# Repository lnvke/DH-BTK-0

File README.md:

# DH-BTK-0
Bluetooth keyboard HID device.

Made this so I can have a wireless keyboard while practicing with ESP-IDF BLE. Split would have given me the opportunity to work with peripheral bluetooth and non-HID communications, something I have never done before.

This is a custom integrated ESP32-C6 SoM based split keyboard using RMK rust mechanical keyboard firmware. Because Zephyr RTOS support for the ESP32-C6 is limited, ZMK firmware is not a viable choice for this project, as the HID (human interface) over GATT protocol has been documented to have conflicts between NimBLE and proprietary Espressif BLE controllers. RMK uses TrouBLE, a rust-based BLE host stack for bluetooth general functionality, which allows for direct interface with esp-radio, taking the role of the connecting link between TrouBLE and the internal host controller interface for bluetooth.
CAD:
https://cad.onshape.com/documents/ec01e30260fb570aa777a2a3 

PCB/Schematic:

(higher quality in SVG)

To make this for yourself, simply download the gerber files found in the production folder (seen as zip files) and export to your fab of choice. I used JLCPCB here. This PCB was designed to be completely double-sided and interchangeable, as to cut down on PCB manufacturing costs. Using JLCPCB's PCB fab MOQ of 5, you can make up to 2 of these keyboards given you have enough components.

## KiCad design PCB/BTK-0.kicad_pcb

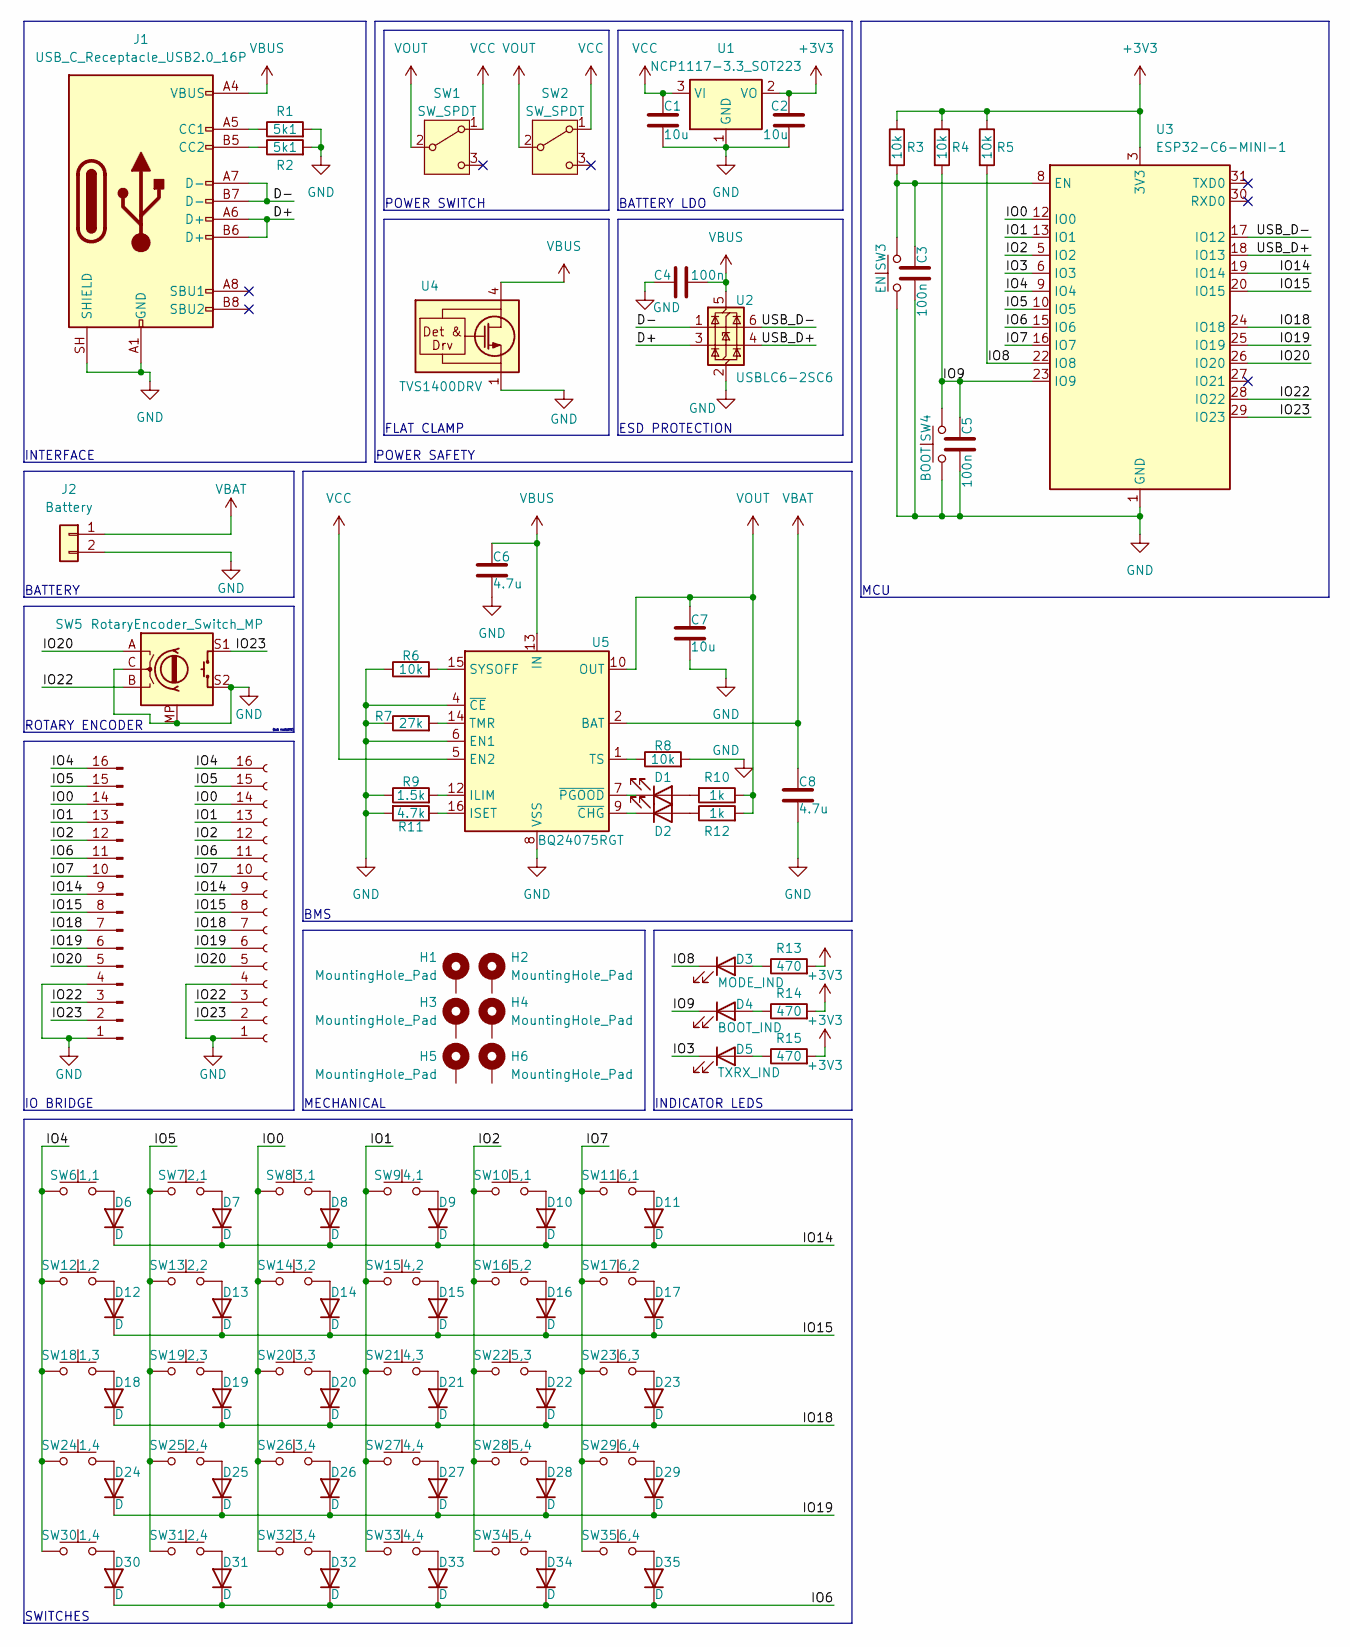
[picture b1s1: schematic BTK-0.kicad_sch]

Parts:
C1, C2, C7: 10u; C_0805_2012Metric
C3, C4, C5: 100n; C_0805_2012Metric
C6, C8: 4.7u; C_0805_2012Metric
D1, D2: LED; LED_0805_2012Metric
D3: MODE_IND; LED_0805_2012Metric
D4: BOOT_IND; LED_0805_2012Metric
D5: TXRX_IND; LED_0805_2012Metric
D6, D7, D8, D9, D10, D11, D12, D13, D14, D15, D16, D17, D18, D19, D20, D21, D22, D23, D24, D25, D26, D27, D28, D29, D30, D31, D32, D33, D34, D35: D; D_0805_2012Metric
H1, H2, H3, H4, H5, H6: MountingHole_Pad; MountingHole_3.2mm_M3_ISO7380
J1: USB_C_Receptacle_USB2.0_16P; GCT_USB4510-03-1-A_REVA
J2: Battery; PinHeader_1x02_P2.54mm_Vertical
J3: Conn_01x16_Pin; PinHeader_1x16_P1.00mm_Vertical
J4: Conn_01x16_Socket; PinHeader_1x16_P1.00mm_Vertical
R1, R2: 5k1; R_0805_2012Metric
R3, R4, R5, R6, R8: 10k; R_0805_2012Metric
R7: 27k; R_0805_2012Metric
R9: 1.5k; R_0805_2012Metric
R10, R12: 1k; R_0805_2012Metric
R11: 4.7k; R_0805_2012Metric
R13, R14, R15: 470; R_0805_2012Metric
SW1, SW2: SW_SPDT; SW_JS102011SAQN
SW3: EN; SW_Tactile_Straight_KSA0Axx1LFTR
SW4: BOOT; SW_PUSH_6mm
SW5: RotaryEncoder_Switch_MP; RotaryEncoder_Alps_EC12E-Switch_Vertical_H20mm_CircularMoun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
SW6: 1,1; Kailh_socket_MX_reversible
SW7: 2,1; Kailh_socket_MX_reversible
SW8: 3,1; Kailh_socket_MX_reversible
SW9: 4,1; Kailh_socket_MX_reversible
SW10: 5,1; Kailh_socket_MX_reversible
SW11: 6,1; Kailh_socket_MX_reversible
SW12: 1,2; Kailh_socket_MX_reversible
SW13: 2,2; Kailh_socket_MX_reversible
SW14: 3,2; Kailh_socket_MX_reversible
SW15: 4,2; Kailh_socket_MX_reversible
SW16: 5,2; Kailh_socket_MX_reversible
SW17: 6,2; Kailh_socket_MX_reversible
SW18: 1,3; Kailh_socket_MX_reversible
SW19: 2,3; Kailh_socket_MX_reversible
SW20: 3,3; Kailh_socket_MX_reversible
SW21: 4,3; Kailh_socket_MX_reversible
SW22: 5,3; Kailh_socket_MX_reversible
SW23: 6,3; Kailh_socket_MX_reversible
SW24, SW30: 1,4; Kailh_socket_MX_reversible
SW25, SW31: 2,4; Kailh_socket_MX_reversible
SW26, SW32: 3,4; Kailh_socket_MX_reversible
SW27, SW33: 4,4; Kailh_socket_MX_reversible
SW28, SW34: 5,4; Kailh_socket_MX_reversible
SW29, SW35: 6,4; Kailh_socket_MX_reversible
U1: NCP1117-3.3_SOT223; SOT-223-3_TabPin2
U2: USBLC6-2SC6; SOT-23-6
U3: ESP32-C6-MINI-1; XCVR_ESP32-C6-MINI-1U-H4
U4: TVS1400DRV; WSON-6-1EP_2x2mm_P0.65mm_EP1x1.6mm
U5: BQ24075RGT; VQFN-16-1EP_3x3mm_P0.5mm_EP1.6x1.6mm

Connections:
+3V3: C2.1, R3.1, R4.1, R5.1, R13.2, R14.2, R15.2, U1.2 (VO), U3.3 (3V3)
/D+: J1.A6 (D+), J1.B6 (D+), U2.3 (I/O2)
/D-: J1.A7 (D-), J1.B7 (D-), U2.1 (I/O1)
/IO0: J3.14, J4.14, SW8.1, SW14.1, SW20.1, SW26.1, SW32.1, U3.12 (IO0)
/IO1: J3.13, J4.13, SW9.1, SW15.1, SW21.1, SW27.1, SW33.1, U3.13 (IO1)
/IO2: J3.12, J4.12, SW10.1, SW16.1, SW22.1, SW28.1, SW34.1, U3.5 (IO2)
/IO3: D5.1 (K), U3.6 (IO3)
/IO4: J3.16, J4.16, SW6.1, SW12.1, SW18.1, SW24.1, SW30.1, U3.9 (IO4)
/IO5: J3.15, J4.15, SW7.1, SW13.1, SW19.1, SW25.1, SW31.1, U3.10 (IO5)
/IO6: D30.1 (K), D31.1 (K), D32.1 (K), D33.1 (K), D34.1 (K), D35.1 (K), J3.11, J4.11, U3.15 (IO6)
/IO7: J3.10, J4.10, SW11.1, SW17.1, SW23.1, SW29.1, SW35.1, U3.16 (IO7)
/IO8: D3.1 (K), R5.2, U3.22 (IO8)
/IO9: C5.1, D4.1 (K), R4.2, SW4.2, U3.23 (IO9)
/IO14: D6.1 (K), D7.1 (K), D8.1 (K), D9.1 (K), D10.1 (K), D11.1 (K), J3.9, J4.9, U3.19 (IO14)
/IO15: D12.1 (K), D13.1 (K), D14.1 (K), D15.1 (K), D16.1 (K), D17.1 (K), J3.8, J4.8, U3.20 (IO15)
/IO18: D18.1 (K), D19.1 (K), D20.1 (K), D21.1 (K), D22.1 (K), D23.1 (K), J3.7, J4.7, U3.24 (IO18)
/IO19: D24.1 (K), D25.1 (K), D26.1 (K), D27.1 (K), D28.1 (K), D29.1 (K), J3.6, J4.6, U3.25 (IO19)
/IO20: J3.5, J4.5, SW5.A, U3.26 (IO20)
/IO22: J3.3, J4.3, SW5.B, U3.28 (IO22)
/IO23: J3.2, J4.2, SW5.S1, U3.29 (IO23)
/USB_D+: U2.4 (I/O2), U3.18 (IO13)
/USB_D-: U2.6 (I/O1), U3.17 (IO12)
GND: C1.2, C2.2, C3.2, C4.1, C5.2, C6.2, C7.2, C8.2, J1.A1 (GND), J1.A12 (GND), J1.B1 (GND), J1.B12 (GND), J1.SH (SHIELD), J2.2, J3.1, J3.4, J4.1, J4.4, R1.2, R2.2, R6.1, R7.1, R8.2, R9.1, R11.2, SW3.1, SW4.1, SW5.C, SW5.MP, SW5.S2, U1.1 (GND), U2.2 (GND), U3.1 (GND), U3.2 (GND), U3.11 (GND), U3.14 (GND), U3.36 (GND), U3.37 (GND), U3.38 (GND), U3.39 (GND), U3.40 (GND), U3.41 (GND), U3.42 (GND), U3.43 (GND), U3.44 (GND), U3.45 (GND), U3.46 (GND), U3.47 (GND), U3.48 (GND), U3.49 (GND), U3.49_1 (GND), U3.49_2 (GND), U3.49_3 (GND), U3.49_4 (GND), U3.49_5 (GND), U3.49_6 (GND), U3.49_7 (GND), U3.49_8 (GND), U3.49_9 (GND), U3.50 (GND), U3.51 (GND), U3.52 (GND), U3.53 (GND), U4.1 (GND), U4.2 (GND), U4.3 (GND), U4.7 (GND), U5.4 (~CE), U5.6 (EN1), U5.8 (VSS), U5.17 (VSS); also elsewhere on the board
unnamed: D1.2 (A), R10.2
unnamed: D1.1 (K), U5.7 (~PGOOD)
unnamed: D2.2 (A), R12.1
unnamed: D2.1 (K), U5.9 (~CHG)
unnamed: D3.2 (A), R13.1
unnamed: D4.2 (A), R14.1
unnamed: D5.2 (A), R15.1
unnamed: D6.2 (A), SW6.2
unnamed: D7.2 (A), SW7.2
unnamed: D8.2 (A), SW8.2
unnamed: D9.2 (A), SW9.2
unnamed: D10.2 (A), SW10.2
unnamed: D11.2 (A), SW11.2
unnamed: D12.2 (A), SW12.2
unnamed: D13.2 (A), SW13.2
unnamed: D14.2 (A), SW14.2
unnamed: D15.2 (A), SW15.2
unnamed: D16.2 (A), SW16.2
unnamed: D17.2 (A), SW17.2
unnamed: D18.2 (A), SW18.2
unnamed: D19.2 (A), SW19.2
unnamed: D20.2 (A), SW20.2
unnamed: D21.2 (A), SW21.2
unnamed: D22.2 (A), SW22.2
unnamed: D23.2 (A), SW23.2
unnamed: D24.2 (A), SW24.2
unnamed: D25.2 (A), SW25.2
unnamed: D26.2 (A), SW26.2
unnamed: D27.2 (A), SW27.2
unnamed: D28.2 (A), SW28.2
unnamed: D29.2 (A), SW29.2
unnamed: D30.2 (A), SW30.2
unnamed: D31.2 (A), SW31.2
unnamed: D32.2 (A), SW32.2
unnamed: D33.2 (A), SW33.2
unnamed: D34.2 (A), SW34.2
unnamed: D35.2 (A), SW35.2
unnamed: J1.A5 (CC1), R1.1
unnamed: J1.B5 (CC2), R2.1
unnamed: C3.1, R3.2, SW3.2, U3.8 (EN)
unnamed: R9.2, U5.12 (ILIM)
unnamed: R11.1, U5.16 (ISET)
unnamed: R6.2, U5.15 (SYSOFF)
unnamed: R7.2, U5.14 (TMR)
unnamed: R8.1, U5.1 (TS)
VBAT: C8.1, J2.1, U5.2 (BAT), U5.3 (BAT)
VBUS: C4.2, C6.1, J1.A4 (VBUS), J1.A9 (VBUS), J1.B4 (VBUS), J1.B9 (VBUS), U2.5 (VBUS), U4.4 (IN), U4.5 (IN), U4.6 (IN), U5.13 (IN)
VCC: C1.1, SW1.1 (A), SW2.1 (A), U1.3 (VI), U5.5 (EN2)
VOUT: C7.1, R10.1, R12.2, SW1.2 (B), SW2.2 (B), U5.10 (OUT), U5.11 (OUT); also elsewhere on the board

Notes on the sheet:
POWER SAFETY
IO BRIDGE
MCU
MECHANICAL
INDICATOR LEDS
ROTARY ENCODER
POWER SWITCH
ESD PROTECTION
(nah really???)
INTERFACE
SWITCHES
FLAT CLAMP
BATTERY
BATTERY LDO
BMS

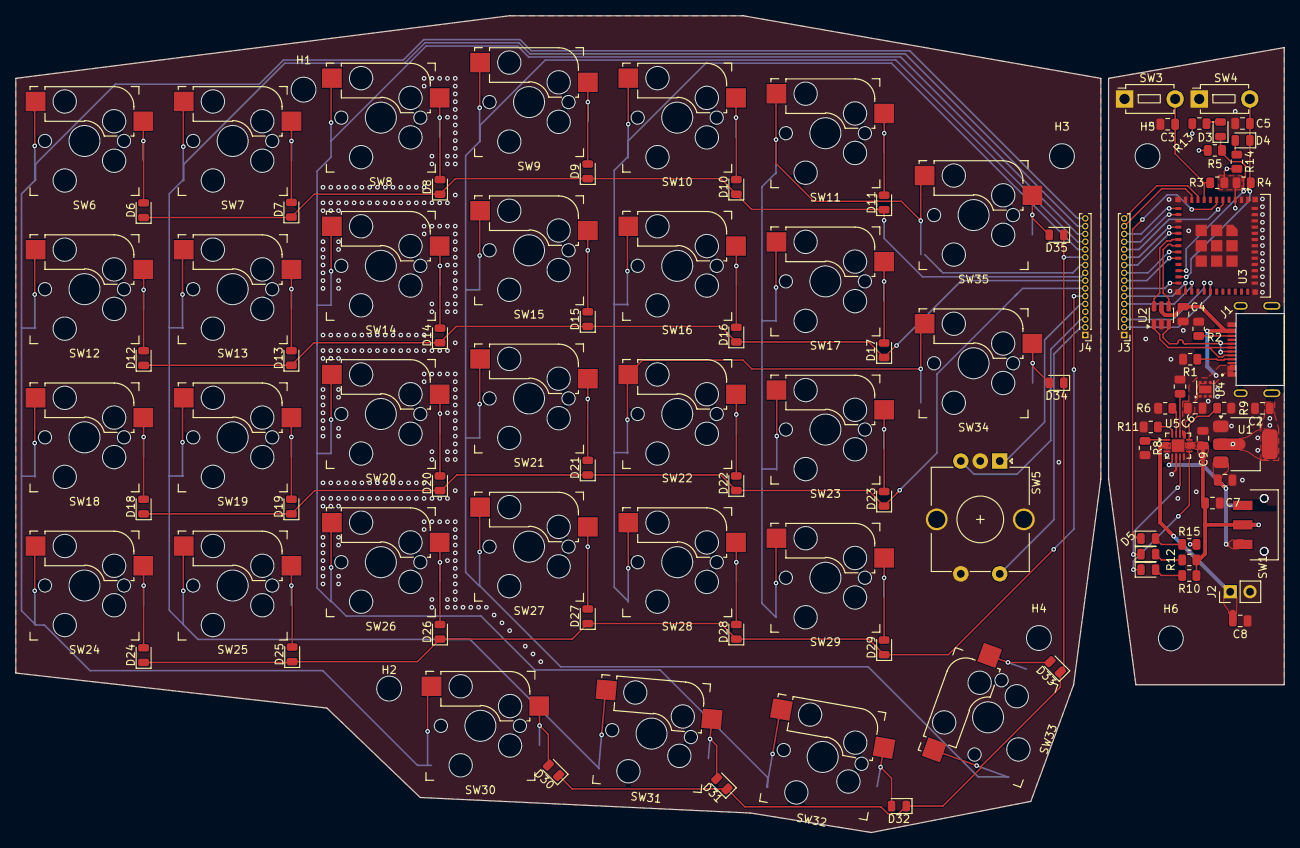
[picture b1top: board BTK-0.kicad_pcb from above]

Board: 4 copper layers, 163.1 x 105.0 mm, 109 parts (1 on the bottom side), 72 nets.

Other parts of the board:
C9: 4.7u; C_0805_2012Metric

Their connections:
GND: C9.2; also elsewhere on the board
VOUT: C9.1; also elsewhere on the board

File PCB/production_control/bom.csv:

Designator,Footprint,Quantity,Value,LCSC Part #
"C1, C2, C7",0805,3,10u,
"C3, C4, C5",0805,3,100n,
"C6, C8, C9",0805,3,4.7u,
"D1, D2",0805,2,LED,
D3,0805,1,MODE_IND,
D4,0805,1,BOOT_IND,
D5,0805,1,TXRX_IND,
J1,GCT_USB4510-03-1-A_REVA,1,USB_C_Receptacle_USB2.0_16P,
J2,PinHeader_1x02_P2.54mm_Vertical,1,Battery,
J3,PinHeader_1x16_P1.00mm_Vertical,1,Conn_01x16_Pin,
"R1, R2",0805,2,5k1,
"R10, R12",0805,2,1k,
R11,0805,1,4.7k,
"R13, R14, R15",0805,3,470,
"R3, R4, R5, R6, R8",0805,5,10k,
R7,0805,1,27k,
R9,0805,1,1.5k,
"SW1, SW2",SW_JS102011SAQN,2,SW_SPDT,
SW3,SW_PUSH_1P1T_6x3.5mm_H4.3_APEM_MJTP1243,1,EN,
SW4,SW_PUSH_1P1T_6x3.5mm_H4.3_APEM_MJTP1243,1,BOOT,
U1,SOT-223-3_TabPin2,1,NCP1117-3.3_SOT223,
U2,SOT-23-6,1,USBLC6-2SC6,
U3,XCVR_ESP32-C6-MINI-1U-H4,1,ESP32-C6-MINI-1,
U4,WSON-6-1EP_2x2mm_P0.65mm_EP1x1.6mm,1,TVS1400DRV,
U5,VQFN-16-1EP_3x3mm_P0.5mm_EP1.6x1.6mm,1,BQ24075RGT,

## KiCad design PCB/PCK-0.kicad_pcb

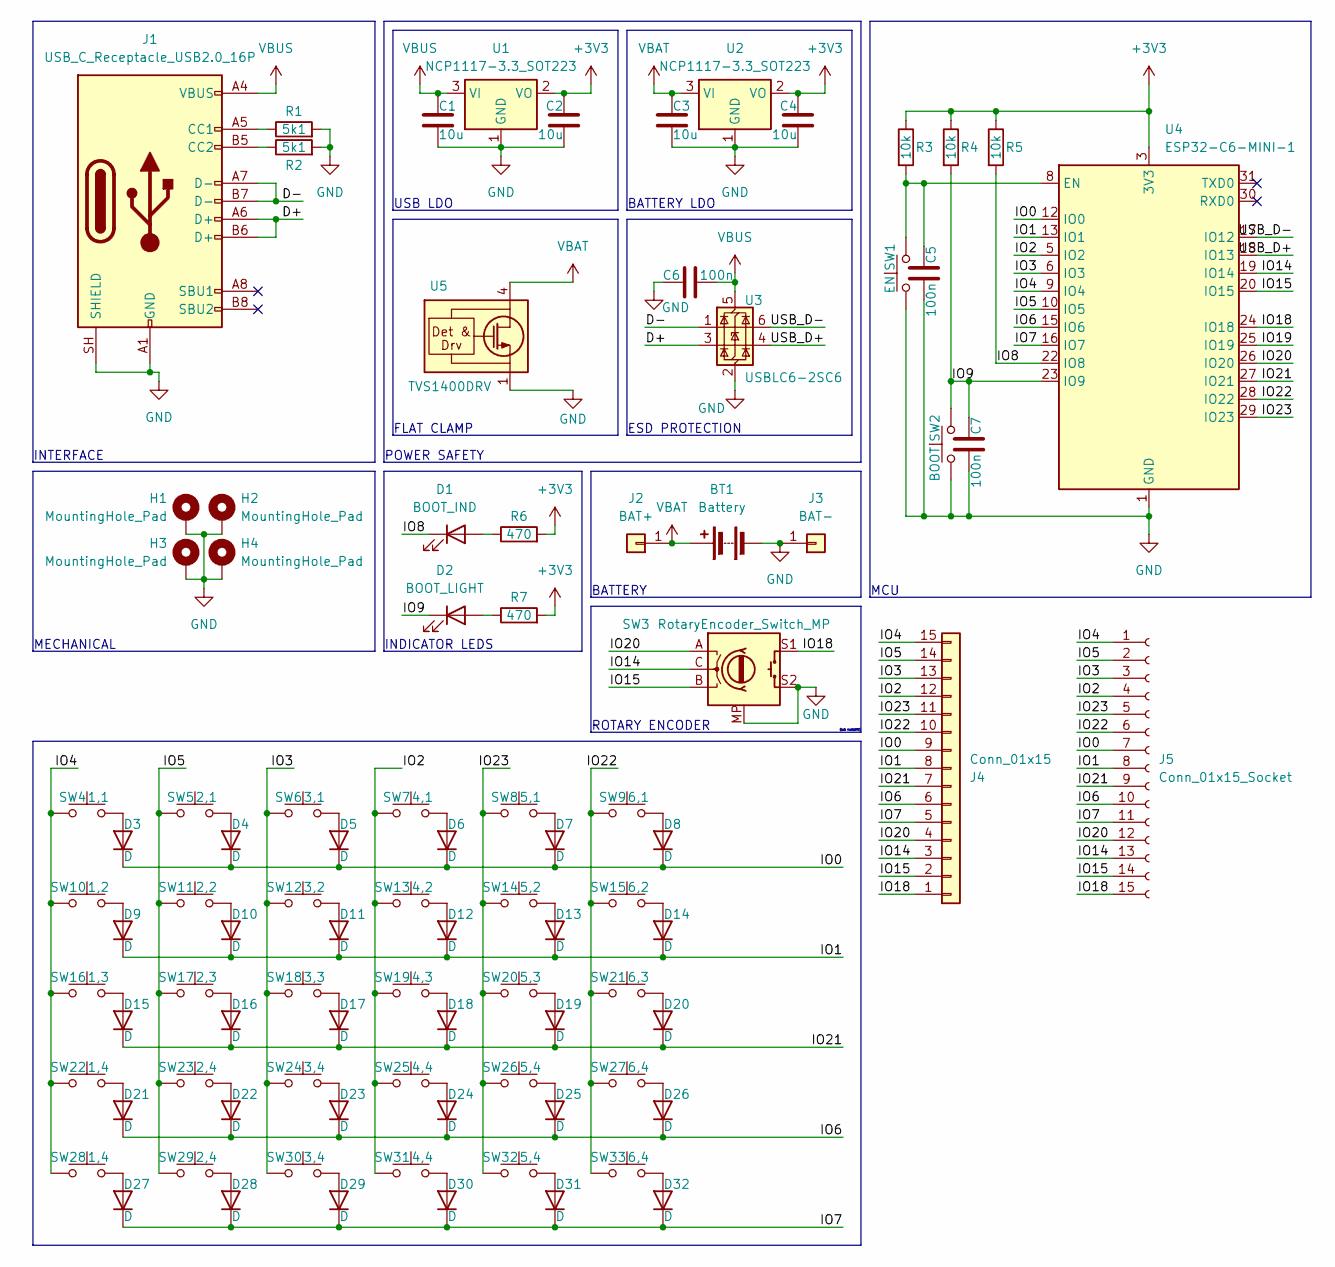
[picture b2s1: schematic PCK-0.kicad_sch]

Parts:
BT1: Battery; PinHeader_1x02_P2.54mm_Horizontal
C1, C2, C3, C4: 10u; C_0805_2012Metric
C5, C6, C7: 100n; C_0805_2012Metric
D1: BOOT_IND; D_0805_2012Metric
D2: BOOT_LIGHT; D_0805_2012Metric
D3, D4, D5, D6, D7, D8, D9, D10, D11, D12, D13, D14, D15, D16, D17, D18, D19, D20, D21, D22, D23, D24, D25, D26, D27, D28, D29, D30, D31, D32: D; D_0805_2012Metric
H1, H2, H3, H4: MountingHole_Pad; MountingHole_3.2mm_M3
J1: USB_C_Receptacle_USB2.0_16P; USB_C_Receptacle_GCT_USB4105-xx-A_16P_TopMnt_Horizontal
J2: BAT+; PinHeader_1x01_P2.54mm_Vertical
J3: BAT-; PinHeader_1x01_P2.54mm_Vertical
J4: Conn_01x15; PinHeader_1x15_P1.00mm_Horizontal
J5: Conn_01x15_Socket; PinSocket_1x15_P1.00mm_Vertical
R1, R2: 5k1; R_0603_1608Metric
R3, R4, R5: 10k; R_0603_1608Metric
R6, R7: 470; R_0603_1608Metric
SW1: EN; SW_Push_SPST_NO_Alps_SKRK
SW2: BOOT; SW_Push_SPST_NO_Alps_SKRK
SW3: RotaryEncoder_Switch_MP; RotaryEncoder_Alps_EC12E-Switch_Vertical_H20mm_CircularMoun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
SW4: 1,1; SW_MX_reversible
SW5: 2,1; SW_MX_reversible
SW6: 3,1; SW_MX_reversible
SW7: 4,1; SW_MX_reversible
SW8: 5,1; SW_MX_reversible
SW9: 6,1; SW_MX_reversible
SW10: 1,2; SW_MX_reversible
SW11: 2,2; SW_MX_reversible
SW12: 3,2; SW_MX_reversible
SW13: 4,2; SW_MX_reversible
SW14: 5,2; SW_MX_reversible
SW15: 6,2; SW_MX_reversible
SW16: 1,3; SW_MX_reversible
SW17: 2,3; SW_MX_reversible
SW18: 3,3; SW_MX_reversible
SW19: 4,3; SW_MX_reversible
SW20: 5,3; SW_MX_reversible
SW21: 6,3; SW_MX_reversible
SW22, SW28: 1,4; SW_MX_reversible
SW23, SW29: 2,4; SW_MX_reversible
SW24, SW30: 3,4; SW_MX_reversible
SW25, SW31: 4,4; SW_MX_reversible
SW26, SW32: 5,4; SW_MX_reversible
SW27, SW33: 6,4; SW_MX_reversible
U1, U2: NCP1117-3.3_SOT223; SOT-223-3_TabPin2
U3: USBLC6-2SC6; SOT-23-6
U4: ESP32-C6-MINI-1; XCVR_ESP32-C6-MINI-1U-H4
U5: TVS1400DRV; WSON-6-1EP_2x2mm_P0.65mm_EP1x1.6mm

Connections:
+3V3: C2.1, C4.1, R3.1, R4.1, R5.1, R6.2, R7.2, U1.2 (VO), U2.2 (VO), U4.3 (3V3)
/D+: J1.A6 (D+), J1.B6 (D+), U3.3 (I/O2)
/D-: J1.A7 (D-), J1.B7 (D-), U3.1 (I/O1)
/IO0: D3.1 (K), D4.1 (K), D5.1 (K), D6.1 (K), D7.1 (K), D8.1 (K), J4.9, J5.7, U4.12 (IO0)
/IO1: D9.1 (K), D10.1 (K), D11.1 (K), D12.1 (K), D13.1 (K), D14.1 (K), J4.8, J5.8, U4.13 (IO1)
/IO2: J4.12, J5.4, SW7.1, SW13.1, SW19.1, SW25.1, SW31.1, U4.5 (IO2)
/IO3: J4.13, J5.3, SW6.1, SW12.1, SW18.1, SW24.1, SW30.1, U4.6 (IO3)
/IO4: J4.15, J5.1, SW4.1, SW10.1, SW16.1, SW22.1, SW28.1, U4.9 (IO4)
/IO5: J4.14, J5.2, SW5.1, SW11.1, SW17.1, SW23.1, SW29.1, U4.10 (IO5)
/IO6: D21.1 (K), D22.1 (K), D23.1 (K), D24.1 (K), D25.1 (K), D26.1 (K), J4.6, J5.10, U4.15 (IO6)
/IO7: D27.1 (K), D28.1 (K), D29.1 (K), D30.1 (K), D31.1 (K), D32.1 (K), J4.5, J5.11, U4.16 (IO7)
/IO8: D1.1 (K), R5.2, U4.22 (IO8)
/IO9: C7.1, D2.1 (K), R4.2, SW2.2, U4.23 (IO9)
/IO14: J4.3, J5.13, SW3.C, U4.19 (IO14)
/IO15: J4.2, J5.14, SW3.B, U4.20 (IO15)
/IO18: J4.1, J5.15, SW3.S1, U4.24 (IO18)
/IO19: U4.25 (IO19)
/IO20: J4.4, J5.12, SW3.A, U4.26 (IO20)
/IO21: D15.1 (K), D16.1 (K), D17.1 (K), D18.1 (K), D19.1 (K), D20.1 (K), J4.7, J5.9, U4.27 (IO21)
/IO22: J4.10, J5.6, SW9.1, SW15.1, SW21.1, SW27.1, SW33.1, U4.28 (IO22)
/IO23: J4.11, J5.5, SW8.1, SW14.1, SW20.1, SW26.1, SW32.1, U4.29 (IO23)
/USB_D+: U3.4 (I/O2), U4.18 (IO13)
/USB_D-: U3.6 (I/O1), U4.17 (IO12)
GND: BT1.2 (-), C1.2, C2.2, C3.2, C4.2, C5.2, C6.1, C7.2, H1.1, H2.1, H3.1, H4.1, J1.A1 (GND), J1.A12 (GND), J1.B1 (GND), J1.B12 (GND), J1.SH (SHIELD), J3.1, R1.2, R2.2, SW1.1, SW2.1, SW3.MP, SW3.S2, U1.1 (GND), U2.1 (GND), U3.2 (GND), U4.1 (GND), U4.2 (GND), U4.11 (GND), U4.14 (GND), U4.36 (GND), U4.37 (GND), U4.38 (GND), U4.39 (GND), U4.40 (GND), U4.41 (GND), U4.42 (GND), U4.43 (GND), U4.44 (GND), U4.45 (GND), U4.46 (GND), U4.47 (GND), U4.48 (GND), U4.49 (GND), U4.49_1 (GND), U4.49_2 (GND), U4.49_3 (GND), U4.49_4 (GND), U4.49_5 (GND), U4.49_6 (GND), U4.49_7 (GND), U4.49_8 (GND), U4.49_9 (GND), U4.50 (GND), U4.51 (GND), U4.52 (GND), U4.53 (GND), U5.1 (GND), U5.2 (GND), U5.3 (GND), U5.7 (GND)
unnamed: D1.2 (A), R6.1
unnamed: D2.2 (A), R7.1
unnamed: D3.2 (A), SW4.2
unnamed: D4.2 (A), SW5.2
unnamed: D5.2 (A), SW6.2
unnamed: D6.2 (A), SW7.2
unnamed: D7.2 (A), SW8.2
unnamed: D8.2 (A), SW9.2
unnamed: D9.2 (A), SW10.2
unnamed: D10.2 (A), SW11.2
unnamed: D11.2 (A), SW12.2
unnamed: D12.2 (A), SW13.2
unnamed: D13.2 (A), SW14.2
unnamed: D14.2 (A), SW15.2
unnamed: D15.2 (A), SW16.2
unnamed: D16.2 (A), SW17.2
unnamed: D17.2 (A), SW18.2
unnamed: D18.2 (A), SW19.2
unnamed: D19.2 (A), SW20.2
unnamed: D20.2 (A), SW21.2
unnamed: D21.2 (A), SW22.2
unnamed: D22.2 (A), SW23.2
unnamed: D23.2 (A), SW24.2
unnamed: D24.2 (A), SW25.2
unnamed: D25.2 (A), SW26.2
unnamed: D26.2 (A), SW27.2
unnamed: D27.2 (A), SW28.2
unnamed: D28.2 (A), SW29.2
unnamed: D29.2 (A), SW30.2
unnamed: D30.2 (A), SW31.2
unnamed: D31.2 (A), SW32.2
unnamed: D32.2 (A), SW33.2
unnamed: J1.A5 (CC1), R1.1
unnamed: J1.B5 (CC2), R2.1
unnamed: C5.1, R3.2, SW1.2, U4.8 (EN)
VBAT: BT1.1 (+), C3.1, J2.1, U2.3 (VI), U5.4 (IN), U5.5 (IN), U5.6 (IN)
VBUS: C1.1, C6.2, J1.A4 (VBUS), J1.A9 (VBUS), J1.B4 (VBUS), J1.B9 (VBUS), U1.3 (VI), U3.5 (VBUS)

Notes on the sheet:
POWER SAFETY
MCU
MECHANICAL
INDICATOR LEDS
ROTARY ENCODER
USB LDO
ESD PROTECTION
(nah really???)
INTERFACE
FLAT CLAMP
BATTERY
BATTERY LDO

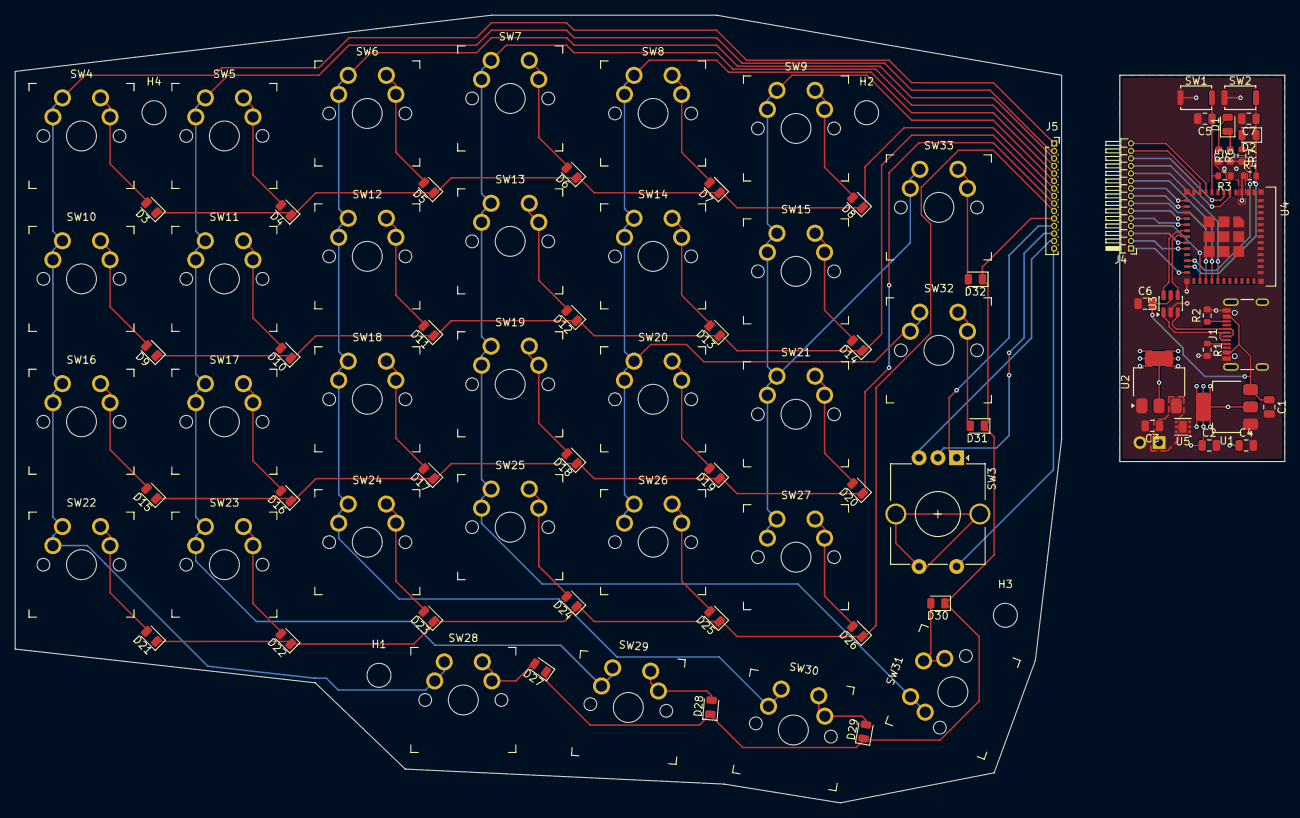
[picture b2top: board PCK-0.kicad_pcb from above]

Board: 4 copper layers, 169.2 x 105.0 mm, 92 parts (1 on the bottom side), 60 nets.

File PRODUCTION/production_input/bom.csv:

Designator,Footprint,Quantity,Value,LCSC Part #
"D10, D11, D12, D13, D14, D15, D16, D17, D18, D19, D20, D21, D22, D23, D24, D25, D26, D27, D28, D29, D30, D31, D32, D33, D34, D35, D6, D7, D8, D9",0805,30,D,
J4,PinHeader_1x16_P1.00mm_Vertical,1,Conn_01x16_Socket,
SW10,Kailh_socket_MX_reversible,1,"5,1",
SW11,Kailh_socket_MX_reversible,1,"6,1",
SW12,Kailh_socket_MX_reversible,1,"1,2",
SW13,Kailh_socket_MX_reversible,1,"2,2",
SW14,Kailh_socket_MX_reversible,1,"3,2",
SW15,Kailh_socket_MX_reversible,1,"4,2",
SW16,Kailh_socket_MX_reversible,1,"5,2",
SW17,Kailh_socket_MX_reversible,1,"6,2",
SW18,Kailh_socket_MX_reversible,1,"1,3",
SW19,Kailh_socket_MX_reversible,1,"2,3",
SW20,Kailh_socket_MX_reversible,1,"3,3",
SW21,Kailh_socket_MX_reversible,1,"4,3",
SW22,Kailh_socket_MX_reversible,1,"5,3",
SW23,Kailh_socket_MX_reversible,1,"6,3",
"SW24, SW30",Kailh_socket_MX_reversible,2,"1,4",
"SW25, SW31",Kailh_socket_MX_reversible,2,"2,4",
"SW26, SW32",Kailh_socket_MX_reversible,2,"3,4",
"SW27, SW33",Kailh_socket_MX_reversible,2,"4,4",
"SW28, SW34",Kailh_socket_MX_reversible,2,"5,4",
"SW29, SW35",Kailh_socket_MX_reversible,2,"6,4",
SW5,RotaryEncoder_Alps_EC12E-Switch_Vertical_H20mm_CircularMountingHoles,1,RotaryEncoder_Switch_MP,
SW6,Kailh_socket_MX_reversible,1,"1,1",
SW7,Kailh_socket_MX_reversible,1,"2,1",
SW8,Kailh_socket_MX_reversible,1,"3,1",
SW9,Kailh_socket_MX_reversible,1,"4,1",
